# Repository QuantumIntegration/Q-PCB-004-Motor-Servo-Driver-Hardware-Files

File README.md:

# Quantum DIY Kit Hardware Files - Motor Servo Driver
## Introduction

This repository contains all the hardware files necessary to build the PCBs and assemble the DIY kits. The PCBs can be ordered from for example [JLCPCB](https://jlcpcb.com/) or [PCBWay](https://www.pcbway.com/). The components can be sourced mostly from [Amazon](https://amazon.com/) or [Digikey](https://digikey.com/), according to the links in the BOM file.

## Download the correct revision

If you are nor familiar with the git version control system, please follow these simple steps to download your version of the DIY kit

<em>1. Click the branch button</em>

<em>2. Select the branch matching your revision</em>

<em>3. Click the Code button</em>

<em>4. Download the ZIP and extract it on your machine</em>

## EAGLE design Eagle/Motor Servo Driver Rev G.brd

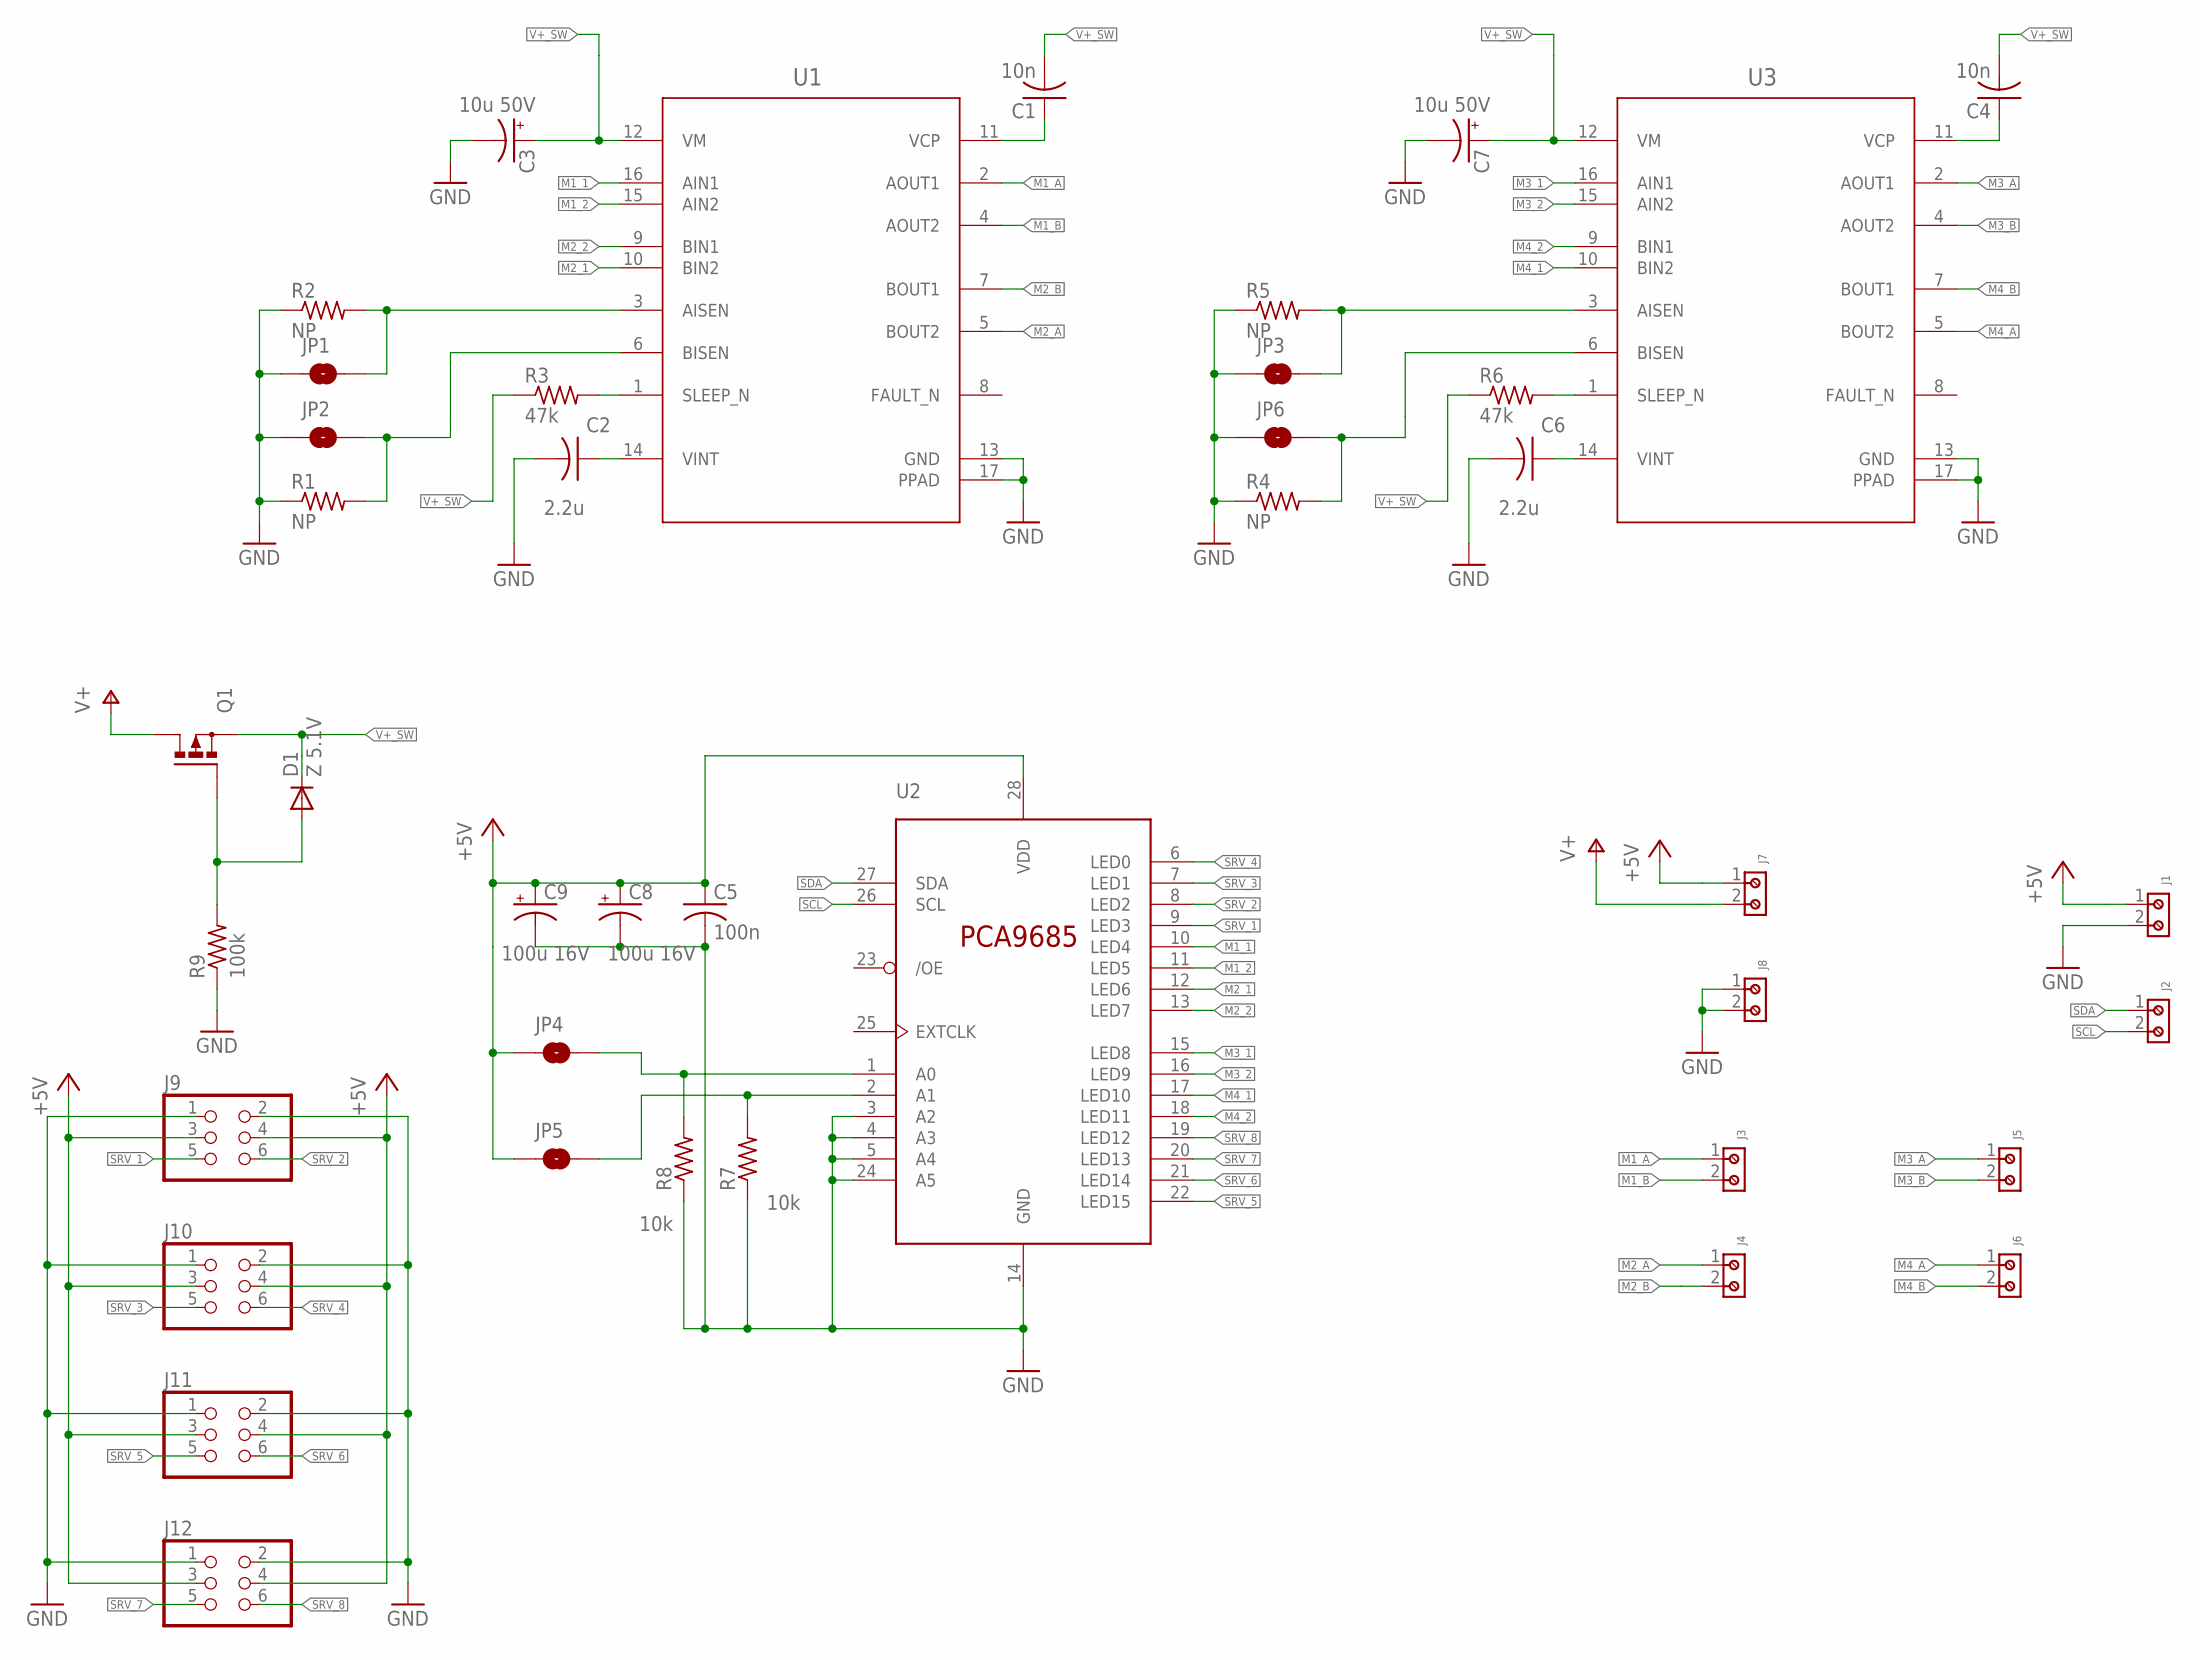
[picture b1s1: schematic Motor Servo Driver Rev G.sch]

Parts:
C1, C4: 10n; C050-024X044
C2, C6: 2.2u; C050-024X044
C3, C7: 10u 50V; E2,5-5
C5: 100n; C050-024X044
C8, C9: 100u 16V; E2,5-5
D1: Z 5.1V; DO41-10
J1, J2, J3, J4, J5, J6, J7, J8: 691214110002
J9, J10, J11, J12: PINHD-2X3; 2X03
JP1, JP2, JP3, JP4, JP5, JP6: JUMPER-SMT_2_NO_SILK; SMT-JUMPER_2_NO_SILK
Q1: PMOSFET_PTO220BV; TO220BV
R1, R2, R4, R5: NP; R1206
R3, R6: 47k; 0207/10
R7, R8: 10k; 0207/10
R9: 100k; 0207/10
U1, U3: Value; PWP0016C_N
U2: PCA9685; TSSOP28

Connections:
+5V: C5.1, C8.+, C9.+, J1.1, J7.1, J9.3, J9.4, J10.3, J10.4, J11.3, J11.4, J12.3, J12.4, JP4.1, JP5.1, U2.28 (VDD)
GND: C2.2, C3.-, C5.2, C6.2, C7.-, C8.-, C9.-, J1.2, J8.1, J8.2, J9.1, J9.2, J10.1, J10.2, J11.1, J11.2, J12.1, J12.2, JP1.1, JP2.1, JP3.1, JP6.1, R1.1, R2.1, R4.1, R5.1, R7.1, R8.1, R9.1, U1.13 (GND), U1.17 (PPAD), U2.3 (A2), U2.4 (A3), U2.5 (A4), U2.14 (GND), U2.24 (A5), U3.13 (GND), U3.17 (PPAD)
M1_1: U1.16 (AIN1), U2.10 (LED4)
M1_2: U1.15 (AIN2), U2.11 (LED5)
M1_A: J3.1, U1.2 (AOUT1)
M1_B: J3.2, U1.4 (AOUT2)
M2_1: U1.10 (BIN2), U2.12 (LED6)
M2_2: U1.9 (BIN1), U2.13 (LED7)
M2_A: J4.1, U1.5 (BOUT2)
M2_B: J4.2, U1.7 (BOUT1)
M3_1: U2.15 (LED8), U3.16 (AIN1)
M3_2: U2.16 (LED9), U3.15 (AIN2)
M3_A: J5.1, U3.2 (AOUT1)
M3_B: J5.2, U3.4 (AOUT2)
M4_1: U2.17 (LED10), U3.10 (BIN2)
M4_2: U2.18 (LED11), U3.9 (BIN1)
M4_A: J6.1, U3.5 (BOUT2)
M4_B: J6.2, U3.7 (BOUT1)
unnamed: JP6.2, R4.2, U3.6 (BISEN)
unnamed: C2.1, U1.14 (VINT)
unnamed: D1.A, Q1.G, R9.2
unnamed: JP3.2, R5.2, U3.3 (AISEN)
unnamed: JP2.2, R1.2, U1.6 (BISEN)
unnamed: C1.1, U1.11 (VCP)
unnamed: JP1.2, R2.2, U1.3 (AISEN)
unnamed: C6.1, U3.14 (VINT)
unnamed: C4.1, U3.11 (VCP)
unnamed: R6.2, U3.1 (SLEEP_N)
unnamed: JP5.2, R7.2, U2.2 (A1)
unnamed: JP4.2, R8.2, U2.1 (A0)
unnamed: R3.2, U1.1 (SLEEP_N)
SCL: J2.2, U2.26 (SCL)
SDA: J2.1, U2.27 (SDA)
SRV_1: J9.5, U2.9 (LED3)
SRV_2: J9.6, U2.8 (LED2)
SRV_3: J10.5, U2.7 (LED1)
SRV_4: J10.6, U2.6 (LED0)
SRV_5: J11.5, U2.22 (LED15)
SRV_6: J11.6, U2.21 (LED14)
SRV_7: J12.5, U2.20 (LED13)
SRV_8: J12.6, U2.19 (LED12)
V+: J7.2, Q1.D
V+_SW: C1.2, C3.+, C4.2, C7.+, D1.C, Q1.S, R3.1, R6.1, U1.12 (VM), U3.12 (VM)

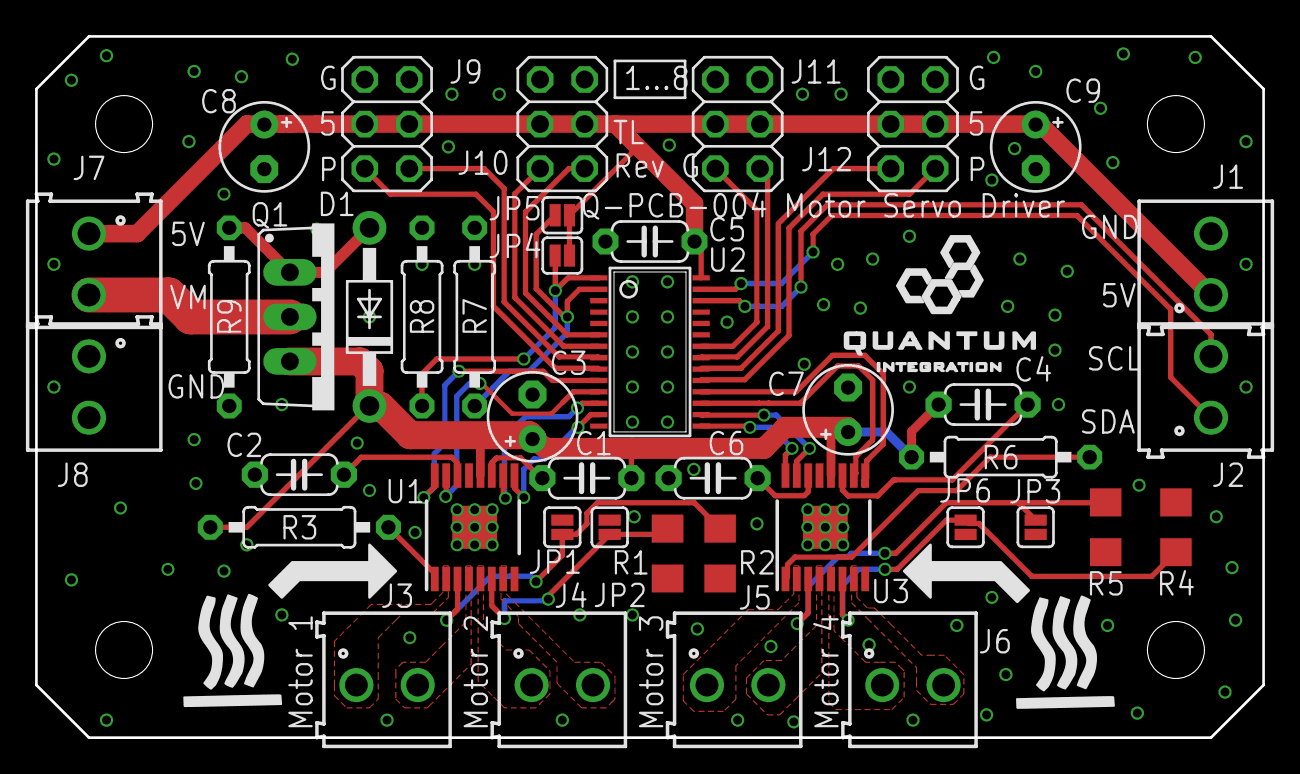
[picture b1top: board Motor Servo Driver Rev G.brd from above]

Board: 2 copper layers, 70.0 x 40.0 mm, 41 parts (0 on the bottom side), 43 nets.

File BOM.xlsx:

Index | Part | Value | Quantitiy | Designators | Package | Comments | Specific Part Reference | Part Link Example
1 | Header |  | 4 | J9, J10, J11, J12 | 0.1 | 2x3, male |  | https://www.amazon.com/MCIGICM-Header-2-45mm-Arduino-Connect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
2 | PCA9685 |  | 1 | U2 | TSSOP-28 | SMT |  | https://www.digikey.com/en/products/detail/nxp-usa-inc/PCA96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
3 | Resistor | 10k | 2 | R7, R8 | 0207/10 | 1/4 W |  | https://www.amazon.com/SIQUK-Resistors-Resistor-Assortment-E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
4 | Resistor | 47k | 2 | R3, R6 | 0207/10 | 1/4 W |  | https://www.amazon.com/SIQUK-Resistors-Resistor-Assortment-E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
5 | Resistor | 100k | 1 | R9 | 0207/10 | 1/4 W |  | https://www.amazon.com/SIQUK-Resistors-Resistor-Assortment-E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
6 | Ceramic Capacitor | 10n | 2 | C1, C4 | 024x044 |  |  | https://www.digikey.com/product-detail/en/kemet/C315C104M5U5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
7 | Ceramic Capacitor | 100n | 1 | C5 | 024x044 |  |  | https://www.digikey.com/product-detail/en/kemet/C315C104M5U5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
8 | Ceramic Capacitor | 2.2u | 2 | C2, C6 | 024x044 |  |  | https://www.digikey.com/product-detail/en/kemet/C315C104M5U5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
9 | Electrolytic Capacitor | 10u | 2 | C3, C7 | E2,5-5 | H: 10mm, 50V |  | https://www.digikey.com/product-detail/en/nichicon/USA1H010M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
10 | Electrolytic Capacitor | 100u | 2 | C8, C9 | E2,5-5 | H: 10mm, 16V |  | https://www.digikey.com/product-detail/en/nichicon/USA1H010M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
11 | Zener Diode | 5.1V | 1 | D1 |  |  |  | https://www.amazon.com/Makeronics-Zener-Diode-Assortment-Val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
12 | Mosfet P-Channel |  | 1 | Q1 | TO-220 | GDS |  | https://www.amazon.com/LARSEBEI-10Types-transistors-Assortme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
13 | Resistor |  | 4 | R1, R2, R4, R5 | 1206 | SMT |  | https://www.amazon.com/Resistor-Ltvystore-Fixed-Assortment-0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
14 | DRV8833PWP |  | 2 | U1, U3 | HTSSOP-16 | SMT |  | https://www.digikey.com/en/products/detail/texas-instruments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
15 | Terminal |  | 8 | J1, J2, J3, J4, J5, J6, J7, J8 |  | 3.50mm, 1x2 |  | https://www.digikey.com/product-detail/en/w%C3%BCrth-elektro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

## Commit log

2021-07-12 iniital commit
2021-07-12 initial content
2021-12-17 added schematic, updated BOM
2022-01-04 added arduino example

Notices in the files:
parts and their libraries:
SparkFun-Jumpers: Licensing: Creative Commons ShareAlike 4.0 International - https://creativecommons.org/licenses/by-sa/4.0
Wurth_Connectors_WR-TBL Rising Cage Clam: Copyright: Würth Elektronik
